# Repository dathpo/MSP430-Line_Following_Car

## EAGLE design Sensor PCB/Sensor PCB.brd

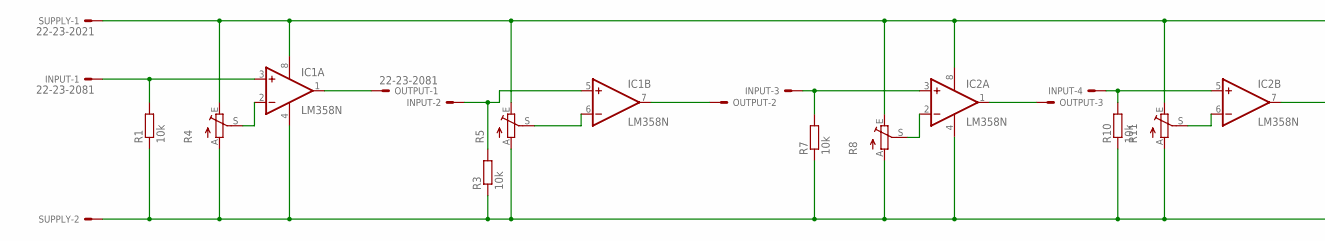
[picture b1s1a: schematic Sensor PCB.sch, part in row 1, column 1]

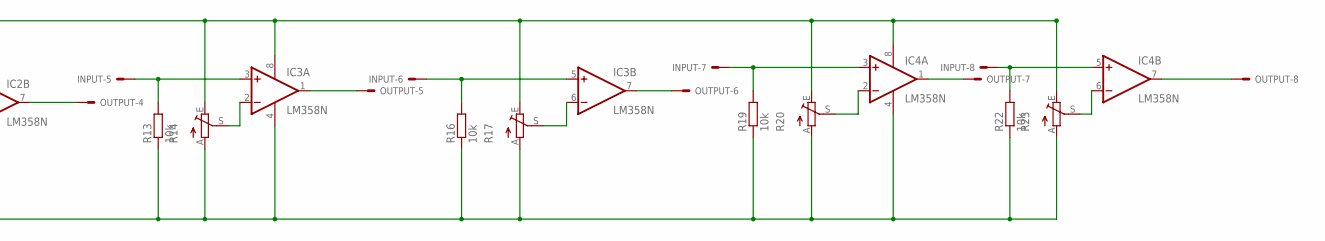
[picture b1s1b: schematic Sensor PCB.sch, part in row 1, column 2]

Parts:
IC1, IC2, IC3, IC4: LM358N; DIL08
INPUT: 22-23-2081
OUTPUT: 22-23-2081
R1, R3, R7, R10, R13, R16, R19, R22: 10k; R1206
R4, R5, R8, R11, R14, R17, R20, R23: TRIM_EU-S64Y; S64Y
SUPPLY: 22-23-2021

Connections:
unnamed: IC1.3 (+IN), INPUT.1, R1.2
unnamed: IC1.2 (-IN), R4.S
unnamed: IC1.8 (V+), IC2.8 (V+), IC3.8 (V+), IC4.8 (V+), R4.E, R5.E, R8.E, R11.E, R14.E, R17.E, R20.E, R23.E, SUPPLY.1
unnamed: IC1.4 (V-), IC2.4 (V-), IC3.4 (V-), IC4.4 (V-), R1.1, R3.1, R4.A, R5.A, R7.1, R8.A, R10.1, R11.A, R13.1, R14.A, R16.1, R17.A, R19.1, R20.A, R22.1, R23.A, SUPPLY.2
unnamed: IC2.7 (OUT), OUTPUT.4
unnamed: IC1.1 (OUT), OUTPUT.1
unnamed: IC1.7 (OUT), OUTPUT.2
unnamed: IC1.5 (+IN), INPUT.2, R3.2
unnamed: IC1.6 (-IN), R5.S
unnamed: IC2.3 (+IN), INPUT.3, R7.2
unnamed: IC2.2 (-IN), R8.S
unnamed: IC2.1 (OUT), OUTPUT.3
unnamed: IC3.2 (-IN), R14.S
unnamed: IC2.5 (+IN), INPUT.4, R10.2
unnamed: IC3.6 (-IN), R17.S
unnamed: IC3.7 (OUT), OUTPUT.6
unnamed: IC2.6 (-IN), R11.S
unnamed: IC4.6 (-IN), R23.S
unnamed: IC3.3 (+IN), INPUT.5, R13.2
unnamed: IC3.1 (OUT), OUTPUT.5
unnamed: IC3.5 (+IN), INPUT.6, R16.2
unnamed: IC4.2 (-IN), R20.S
unnamed: IC4.3 (+IN), INPUT.7, R19.2
unnamed: IC4.1 (OUT), OUTPUT.7
unnamed: IC4.5 (+IN), INPUT.8, R22.2
unnamed: IC4.7 (OUT), OUTPUT.8

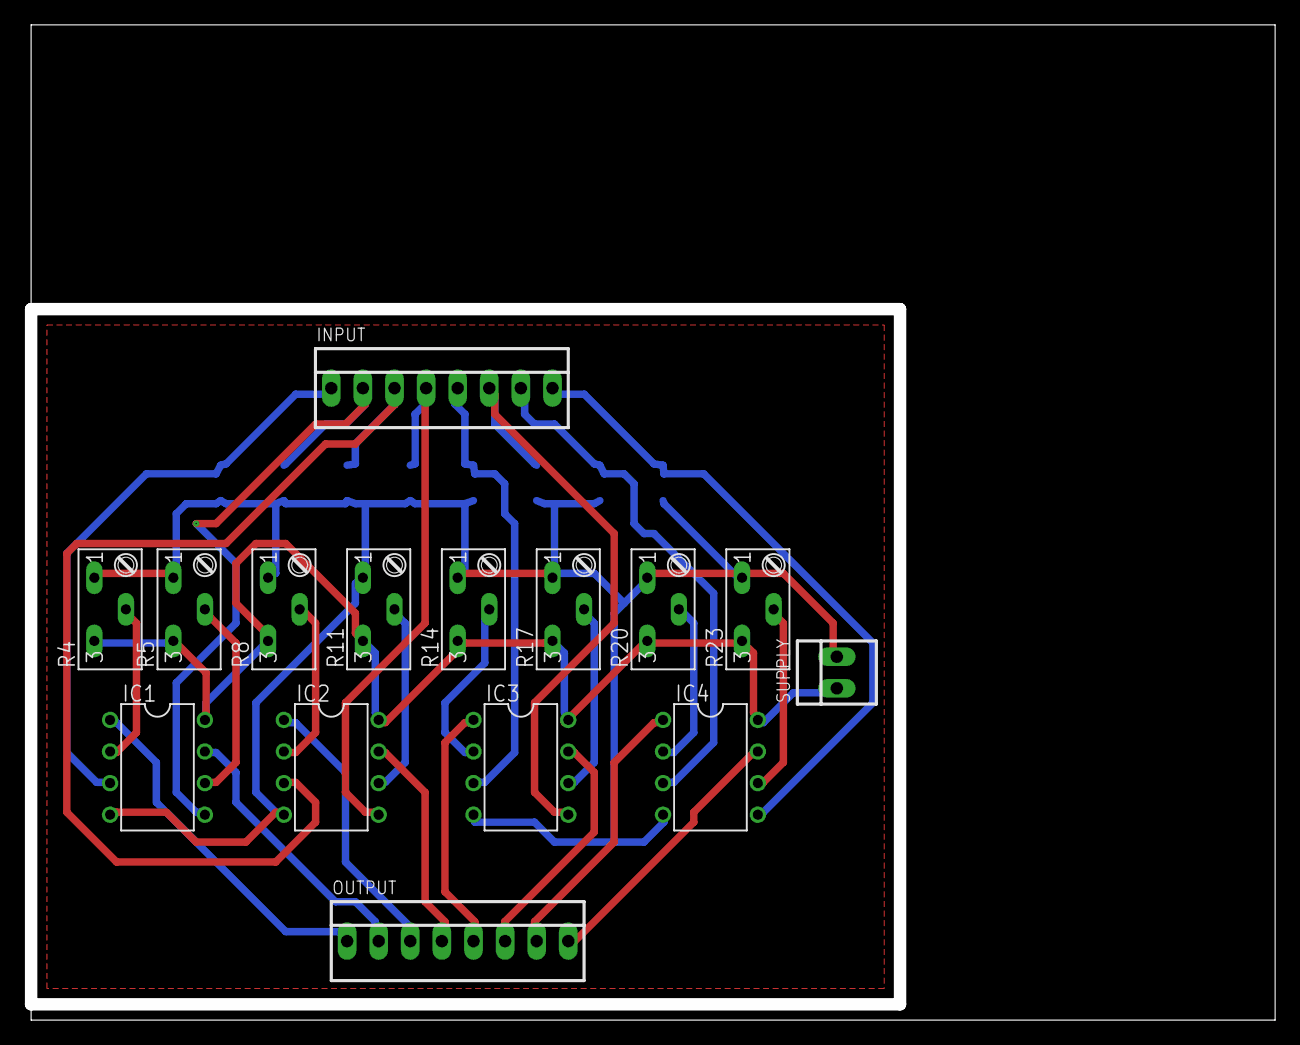
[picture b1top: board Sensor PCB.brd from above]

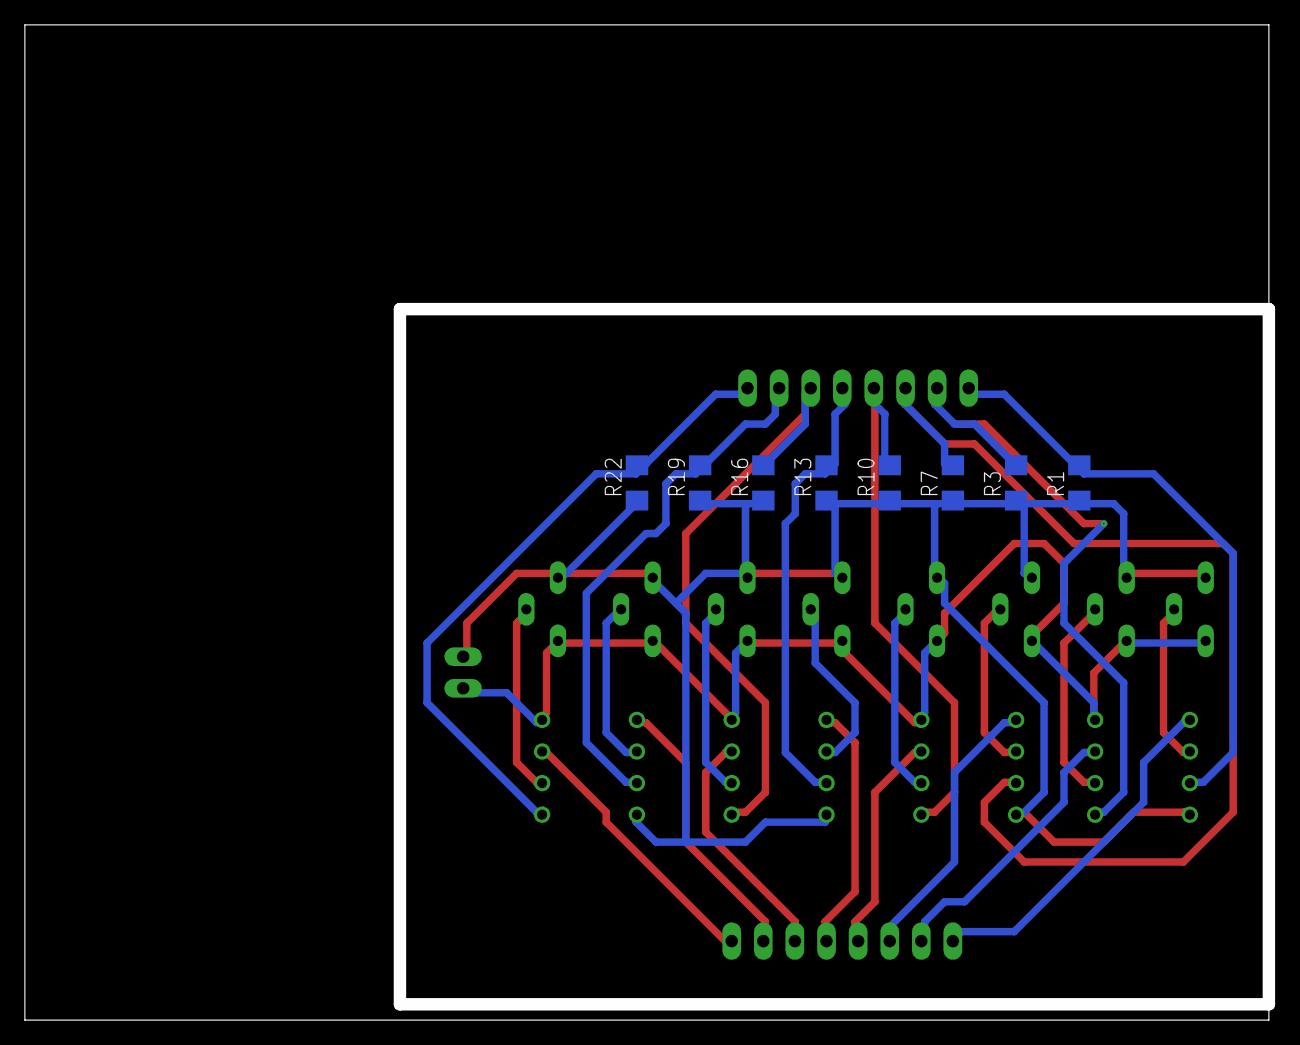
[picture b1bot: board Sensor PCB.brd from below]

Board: 2 copper layers, 99.5 x 79.0 mm, 23 parts (8 on the bottom side), 26 nets.

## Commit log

2017-03-17 Added current working Servo code
2017-04-12 Tidy up project, add sensor PCB Eagle files, servo and motor mains + Jack's
2017-04-12 Best working motor code, cleaned project files
2017-04-12 (pls) delet this
2017-04-12 .gitignore updated
2017-04-20 New Energia folder, latest version is CX318.ino
